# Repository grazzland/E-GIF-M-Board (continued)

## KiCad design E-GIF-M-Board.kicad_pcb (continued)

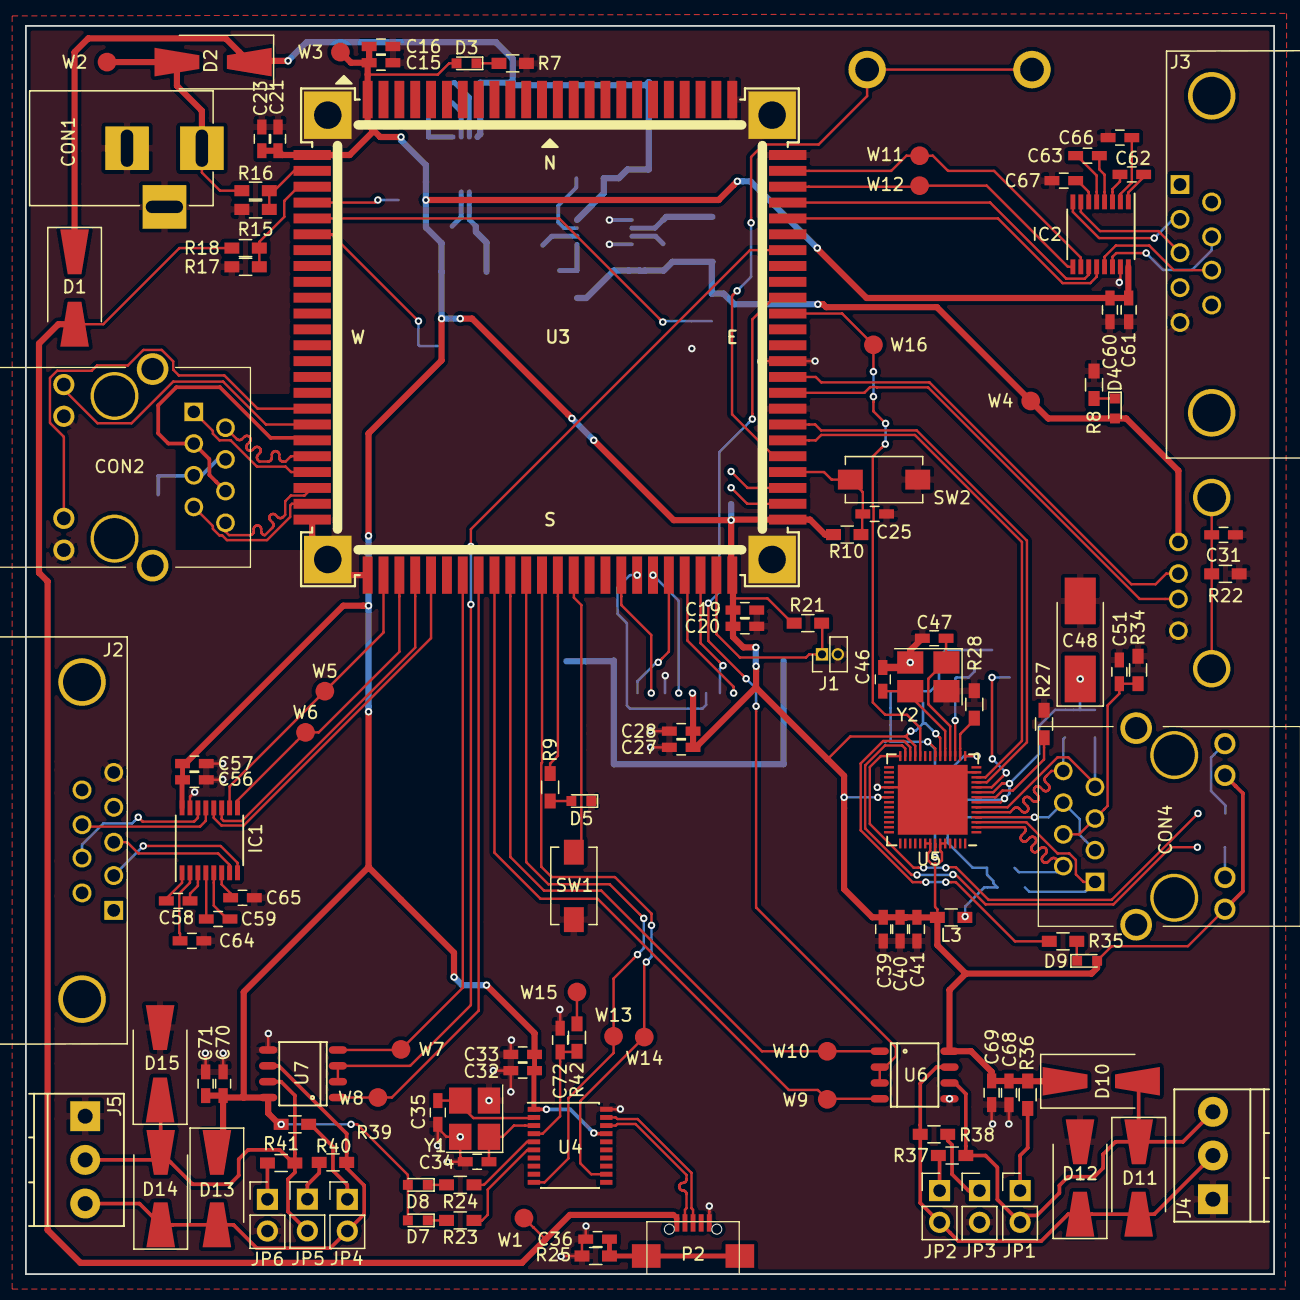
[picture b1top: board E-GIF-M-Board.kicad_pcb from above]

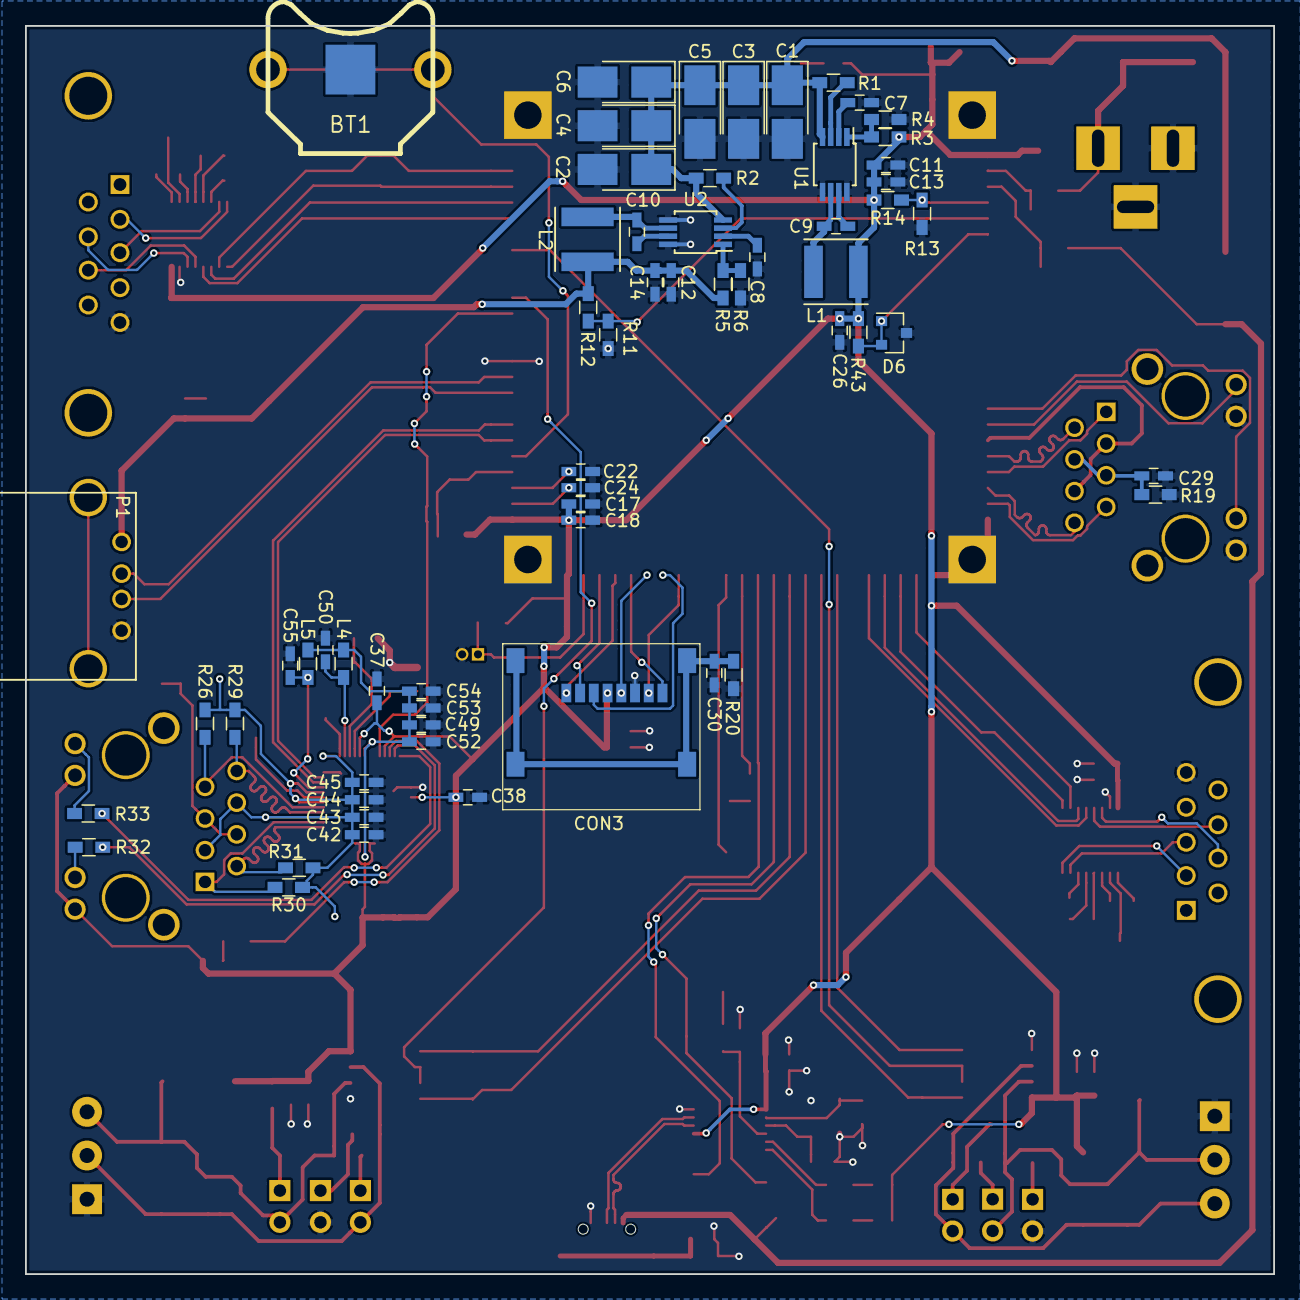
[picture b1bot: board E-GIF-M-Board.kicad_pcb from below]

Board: 2 copper layers, 100.0 x 100.0 mm, 182 parts (62 on the bottom side), 128 nets.

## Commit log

2017-01-16 Added KiCad project with the work done so far. Done the power module. Modified a template for the schematic to add university logo.
2017-01-16 Created branch for Aria Module schematic. Done the VCC, GND and Micro SD conections.
2017-01-17 Added MCP2200, serial to usb converter for debug.
2017-01-18 I will merge and move the interfaces on a new sheet. Modified the schematic of a RJ45 Connector to be the same as the one used in Acme documentation.
2017-01-18 Moved and connected the Debug, MicroSD and EthernetIN(EthIN) in the Interfaces schematic.
2017-01-23 Added schematic component for LAN9500A and started to work on the sheet for interfacing it.
2017-01-29 Finished LAN9500A ETH to USB interface sheet.
2017-01-30 Finished interfaces.
    Finished MAX3232 serial to RS232 interface.
    Finished ST3485 serial to RS485 interface.
2017-01-30 .bak ignore rule
    Ignore bak files
2017-01-30 Added some info text.
2017-02-05 Added to scheamtic.
    Added reset circuit for Aiya, power led for 3V3 line, USB type A connectors for USBB and USBC.
2017-02-10 Schematic correction
    Corrected the direction on some signals. Added a pin header for general development.
2017-02-16 Modified LAN9500A schematic.
    Modified the schematic for the USB to Ethernet converter.
2017-02-23 Schematic changes. PCB in process of making.
    Removed LAN9500A Jtag. Removed Aria G25 pinout. Removed USB connectors. Added rezistors to USB/ETH/ySD shields.
2017-02-24 Modified USB/ETH label names.
2017-02-28 Finished first version of PCB.
    Modified RJ45 footprint.
2017-03-02 Modified buck circuit on board.
2017-03-05 Removed some capacitors.
2017-03-07 Modified schematic. v1.1
2017-03-09 Modified board. v1.1 to reflect the schematic change.
